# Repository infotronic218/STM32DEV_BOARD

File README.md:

# STM32 Custom development board design with Kicad

This is a board designed with STM32 MCU for learning purpose. The board has temperature sensors and accessible GPIOS.
The on board sensors are :
* Humidity and Temperature sensor Si7020-A20(I2C Interface)
* NTC Resistor for measuring temperature with Analog INPUT
* LDR Resistor for measuring the light
* DIP Switchs 2 columns 

## TOP VIEW OF THE 3D

## BOTTOM VIEW OF THE 3D

## Board Layout

# Feel free to contact me for embedded electronics projects or any job opportinuty. I will be glad to contribute  [Link to my portfolio](https://oussenisawadogo.web.app).

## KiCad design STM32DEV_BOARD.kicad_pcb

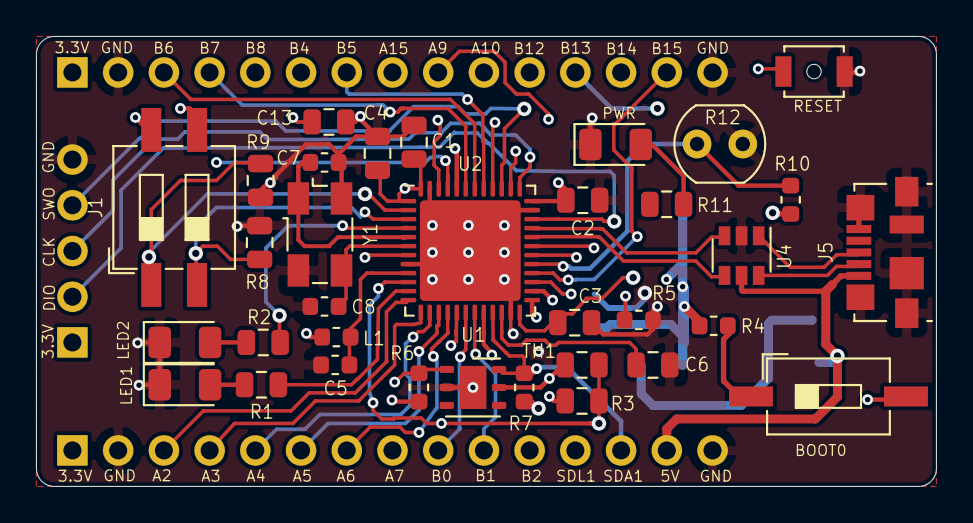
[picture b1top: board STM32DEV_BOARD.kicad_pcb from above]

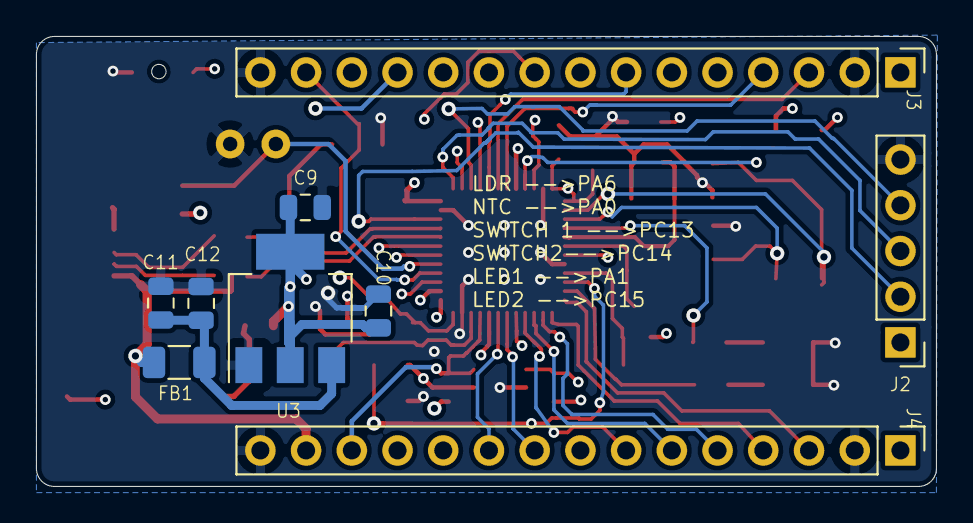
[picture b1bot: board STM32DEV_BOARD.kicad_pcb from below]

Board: 4 copper layers, 50.0 x 25.0 mm, 43 parts (9 on the bottom side), 50 nets.

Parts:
C1, C2, C3, C4, C13: 100n; C_0805_2012Metric
C5: 22pF; C_0603_1608Metric
C6, C9, C10: 2.2u; C_0805_2012Metric
C7, C8: 12pF; C_0603_1608Metric
C11: 0.1u; C_0805_2012Metric
C12: 4.7u; C_0805_2012Metric
FB1: Ferrite_Bead_Small; L_1206_3216Metric
J1: button; SW_DIP_SPSTx02_Slide_6.7x6.64mm_W8.61mm_P2.54mm_LowProfile
J2: DEBUG; PinHeader_1x05_P2.54mm_Vertical
J3, J4: Conn_01x15_Female; PinHeader_1x15_P2.54mm_Vertical
J5: USB_B_Micro; USB_Micro-B_Molex_47346-0001
L1: 33uh; L_0603_1608Metric
LED1, LED2, LED3: LED; LED_1206_3216Metric
R1, R2, R3, R11: 1k; R_0805_2012Metric
R4: 1k; R_0603_1608Metric
R5, R6, R7, R10: 10k; R_0603_1608Metric
R8, R9: 10k; R_0805_2012Metric
R12: VT93xx; R_LDR_4.9x4.2mm_P2.54mm_Vertical
S1: BOOT0; SW_DIP_SPSTx01_Slide_6.7x4.1mm_W8.61mm_P2.54mm_LowProfile
SW1: RESET; SW_SPST_B3U-1000P-B
TH1: 10K; R_0805_2012Metric
U1: Si7020-A20; DFN-6-1EP_3x3mm_P1mm_EP1.5x2.4mm
U2: STM32F411CCUx; QFN-48-1EP_7x7mm_P0.5mm_EP5.6x5.6mm
U3: AMS1117-3.3; SOT-223-3_TabPin2
U4: USBLC6-2SC6; SOT-23-6
Y1: 8MHz; Crystal_SMD_Abracon_ABM3B-4Pin_5.0x3.2mm

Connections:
+3.3VA: C5.1, L1.2, U2.9
+3V3: C1.1, C2.1, C3.1, C4.1, C9.1, C10.1, J1.3, J1.4, J2.1, J3.1, J4.1, L1.1, R4.2, R6.1, R7.1, R10.1, TH1.1, U1.5, U2.1, U2.24, U2.36, U2.48, U3.2
+5V: FB1.2, J4.14, J5.1, U4.5
B1: J1.1, R9.1, U2.2
B2: J1.2, R8.1, U2.3
BOOT0: R5.1, S1.2, U2.44
D1: R1.1, U2.11
D2: R2.1, U2.4
D+: U2.33, U4.3
D-: U2.32, U4.4
GND: C1.2, C2.2, C3.2, C4.2, C5.2, C6.2, C7.2, C8.2, C9.2, C10.2, C11.2, C12.2, C13.2, J2.5, J3.2, J3.15, J4.2, J4.15, J5.5, J5.6, LED1.1, LED2.1, LED3.1, R3.2, R5.2, R8.2, R9.2, R12.2, SW1.1, U1.2, U1.7, U2.8, U2.23, U2.35, U2.47, U2.49, U3.1, U4.2, Y1.2, Y1.4
LDR: R10.2, R12.1, U2.29
NRST: C13.1, SW1.2, U2.7
NTC: R3.1, TH1.2, U2.10
unnamed: C6.1, U2.22
unnamed: C11.1, C12.1, FB1.1, U3.3
unnamed: LED1.2, R1.2
unnamed: LED2.2, R2.2
unnamed: LED3.2, R11.2
unnamed: R4.1, S1.1
PA4: J4.5, U2.14
PA9: J3.9, U2.30
PA10: J3.10, U2.31
PA15: J3.8, U2.38
PB0: J4.9, U2.18
PB1: J4.10, U2.19
PB2: J4.11, U2.20
PB4: J3.6, U2.40
PB5: J3.7, U2.41
PB8: J3.5, U2.45
PB12: J3.11, U2.25
PB13: J3.12, U2.26
PB14: J3.13, U2.27
PB15: J3.14, U2.28
RX1: J3.4, U2.43
RX2: J4.4, U2.13
SDA1: J4.12, R6.2, U1.1, U2.46
SDL1: J4.13, R7.2, U1.6, U2.21
SPI1_MISO: J4.7, U2.16
SPI1_MOSI: J4.8, U2.17
SPI1_SCK: J4.6, U2.15
SWCLK: J2.3, U2.37
SWDIO: J2.2, U2.34
SWO: J2.4, U2.39
TX1: J3.3, U2.42
TX2: J4.3, U2.12
USB_+: J5.3, U4.1
USB_-: J5.2, U4.6
Y1: C7.1, U2.5, Y1.1
Y2: C8.1, U2.6, Y1.3

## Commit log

2021-06-01 First Commit of the project
2021-06-01 Making update
2021-06-01 Adding portfolio linko
